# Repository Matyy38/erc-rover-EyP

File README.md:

---
titulo: Rover ERC — subsistema de Electrónica y Potencia
estado: vigente
fecha: 2026-10-26
fuente: migracion.md (árbol y mapeo de los cuatro documentos fuente)
---

# Rover ERC — Electrónica y Potencia

Documentación del subsistema de Electrónica y Potencia del rover del European Rover Challenge
(IEEE ITBA I+D). Dos frentes: el **rover final** (40 kg, bus de 24 V, swerve de 4 ruedas) y el **modelo a
escala**, que es un instrumento de medición para cerrar la especificación de motores sin comprar
motores de tamaño real a ciegas.

**Empezá por [00-contexto/00-contexto-maestro.md](00-contexto/00-contexto-maestro.md).** Tiene el
estado, los conflictos abiertos y el mapa.

---

## Árbol

```
rover-erc/
├── README.md
├── CLAUDE.md
├── 00-contexto/
│   ├── 00-contexto-maestro.md
│   ├── 01-alcance-y-fronteras.md
│   ├── 02-filosofia-de-diseno.md
│   ├── 03-conflictos-abiertos.md
│   ├── 04-decisiones-descartadas.md
│   └── 05-principios-transversales.md
├── 10-rover-final/
│   ├── 10-locomocion/
│   │   ├── requisitos-motor.md
│   │   └── candidatos-motores.md
│   └── 20-potencia/
│       ├── presupuesto-corriente.md
│       └── cableado-y-protecciones.md
├── 20-modelo-escala/
│   ├── 00-estado-actual.md
│   ├── 10-metodologia-similitud.md
│   ├── 20-electronica/
│   │   ├── arquitectura-electrica.md
│   │   ├── encoders-pcnt.md
│   │   ├── drivers-bts7960.md
│   │   ├── direccion-swerve-servos.md
│   │   ├── sensado-corriente.md
│   │   ├── protecciones-desacople.md
│   │   ├── tmcs1126-datasheet.pdf
│   │   └── PCNT_ESP32_Guia_Rover.pdf
│   ├── 30-pcb/
│   │   ├── especificacion.md
│   │   ├── decisiones-layout.md
│   │   ├── mapa-conectores.md
│   │   ├── bom.md
│   │   └── pendientes-de-verificacion.md
│   ├── 40-firmware/
│   │   ├── mapa-gpio.md
│   │   ├── test-ads1115/
│   │   └── test-mpu6050/
│   └── 50-ensayos/
│       ├── instrumentacion.md
│       └── plan-de-ensayos.md
├── 30-componentes/
├── 40-proveedores-costos/
├── 90-archivo/
│   ├── analisis-sensado-superado.md
│   ├── migracion-2026-09-16.md
│   └── fuentes-originales/
├── audiovisual-presentacion/
└── pcb_V1/
```

---

## Índice

### 00-contexto

| Archivo | Qué tiene |
|---|---|
| [00-contexto-maestro.md](00-contexto/00-contexto-maestro.md) | Documento raíz: estado de los dos frentes, conflictos abiertos, instrumentación, próximos pasos y mapa del repo. |
| [01-alcance-y-fronteras.md](00-contexto/01-alcance-y-fronteras.md) | Qué entra y qué no en el subsistema, con la tabla de interfaces con Mecánica. |
| [02-filosofia-de-diseno.md](00-contexto/02-filosofia-de-diseno.md) | Las reglas no negociables y dónde se aplica cada una. |
| [03-conflictos-abiertos.md](00-contexto/03-conflictos-abiertos.md) | Los tres conflictos que bloquean decisiones y la consulta consolidada a Mecánica. |
| [04-decisiones-descartadas.md](00-contexto/04-decisiones-descartadas.md) | Tabla única de lo que se evaluó y no quedó, con el motivo. |
| [05-principios-transversales.md](00-contexto/05-principios-transversales.md) | Las catorce reglas ganadas en el proyecto que aplican más allá de su caso. |

### 10-rover-final

| Archivo | Qué tiene |
|---|---|
| [10-locomocion/requisitos-motor.md](10-rover-final/10-locomocion/requisitos-motor.md) | Torque, velocidad y potencia por rueda; discrepancias de diámetro; implicancias eléctricas. |
| [10-locomocion/candidatos-motores.md](10-rover-final/10-locomocion/candidatos-motores.md) | Estado por candidato, criterio de reducción y criterio de búsqueda del reemplazo. |
| [20-potencia/presupuesto-corriente.md](10-rover-final/20-potencia/presupuesto-corriente.md) | Del torque medido a la corriente de la PDB: escenarios, techo de tracción, potencia continua. |
| [20-potencia/cableado-y-protecciones.md](10-rover-final/20-potencia/cableado-y-protecciones.md) | Calibres, fusibles y la cadena conector-fusible-cable del rover final. |

### 20-modelo-escala

| Archivo | Qué tiene |
|---|---|
| [00-estado-actual.md](20-modelo-escala/00-estado-actual.md) | Estado de validación de la placa por bloque y cambios confirmados respecto del PDF. |
| [10-metodologia-similitud.md](20-modelo-escala/10-metodologia-similitud.md) | λ vigente, revisión de escala por la masa real, altura del CM y constantes recalculadas. |
| [20-electronica/arquitectura-electrica.md](20-modelo-escala/20-electronica/arquitectura-electrica.md) | Cadena de potencia, rieles y presupuesto del riel de 3,3 V. |
| [20-electronica/encoders-pcnt.md](20-modelo-escala/20-electronica/encoders-pcnt.md) | Acondicionamiento de los ocho canales y uso del periférico PCNT. |
| [20-electronica/drivers-bts7960.md](20-modelo-escala/20-electronica/drivers-bts7960.md) | Habilitaciones, estado del canal 4 en el arranque (V1) y desacople local. |
| [20-electronica/direccion-swerve-servos.md](20-modelo-escala/20-electronica/direccion-swerve-servos.md) | Margen del riel de servos (V3), el PTC único y el estado en el arranque. |
| [20-electronica/sensado-corriente.md](20-modelo-escala/20-electronica/sensado-corriente.md) | TMCS1126B4: qué mide, rango, acondicionamiento, umbral de OC (V9) y calibración. |
| [20-electronica/protecciones-desacople.md](20-modelo-escala/20-electronica/protecciones-desacople.md) | Capas de protección, polaridad inversa (V2), TVS (V5, V6), inrush del relé (V7). |
| [20-electronica/tmcs1126-datasheet.pdf](20-modelo-escala/20-electronica/tmcs1126-datasheet.pdf) | Hoja de datos del TMCS1126 (SBOSAF3D). |
| [20-electronica/PCNT_ESP32_Guia_Rover.pdf](20-modelo-escala/20-electronica/PCNT_ESP32_Guia_Rover.pdf) | Guía de uso del periférico PCNT del ESP32 para los encoders. |
| [30-pcb/especificacion.md](20-modelo-escala/30-pcb/especificacion.md) | Datos generales, corrientes de diseño y anchos de pista. |
| [30-pcb/decisiones-layout.md](20-modelo-escala/30-pcb/decisiones-layout.md) | Masas en estrella, ruteo del TMCS1126, potencia, analógico y mecánica. |
| [30-pcb/mapa-conectores.md](20-modelo-escala/30-pcb/mapa-conectores.md) | Tabla completa de J1 a J19, calibre y fusible del cable soldado en J1 y J4..J7, y convenciones de cableado. |
| [30-pcb/bom.md](20-modelo-escala/30-pcb/bom.md) | Lista por referencia, ítems sin valor definido y compras fuera de placa. |
| [30-pcb/pendientes-de-verificacion.md](20-modelo-escala/30-pcb/pendientes-de-verificacion.md) | Los doce puntos V1 a V12, cómo se confirma cada uno y dónde se discute. |
| [40-firmware/mapa-gpio.md](20-modelo-escala/40-firmware/mapa-gpio.md) | **Fuente única de verdad del pinout**, con la estrategia de arranque seguro. |
| [40-firmware/test-ads1115/](20-modelo-escala/40-firmware/test-ads1115/test-ads1115.ino) | Prueba simple del ADS1115: escaneo I2C y tensión de los cuatro canales cada 0,5 s. |
| [40-firmware/test-mpu6050/](20-modelo-escala/40-firmware/test-mpu6050/test-mpu6050.ino) | Prueba del MPU6050: escaneo I2C, prueba estática con pasa / no pasa, ángulos a 100 Hz. |
| [50-ensayos/instrumentacion.md](20-modelo-escala/50-ensayos/instrumentacion.md) | Cadena de medición, tiro en barra, instrumento externo y riesgos de medición. |
| [50-ensayos/plan-de-ensayos.md](20-modelo-escala/50-ensayos/plan-de-ensayos.md) | Ensayo de ángulo de deslizamiento, Ensayo A fuera de la PDB y próximos pasos. |

### Carpetas por llenar y archivo

| Archivo | Qué tiene |
|---|---|
| [30-componentes/README.md](30-componentes/README.md) | Ficha por componente y enlaces a hojas de datos. Vacía. |
| [40-proveedores-costos/README.md](40-proveedores-costos/README.md) | Proveedores y costos de importación. Vacía. |
| [90-archivo/README.md](90-archivo/README.md) | Versiones superadas y ramas muertas. **No usar como fuente.** |
| [90-archivo/analisis-sensado-superado.md](90-archivo/analisis-sensado-superado.md) | El análisis que suponía que el TMCS1126 medía el total de la PDB, con su nota de trazabilidad. |
| [90-archivo/migracion-2026-09-16.md](90-archivo/migracion-2026-09-16.md) | Plan con el que se armó este árbol a partir de los cuatro documentos fuente. |
| [90-archivo/fuentes-originales/README.md](90-archivo/fuentes-originales/README.md) | Los cuatro documentos previos a la migración, sin tocar. |

### Material para el equipo

| Archivo | Qué tiene |
|---|---|
| [audiovisual-presentacion/guia-ingreso-EyP-2026-09.docx](audiovisual-presentacion/guia-ingreso-EyP-2026-09.docx) | Guía de ingreso: resumen del repo para ponerse al día. Corte al 28-sep-2026; si no coincide con el repo, manda el repo. |
| [audiovisual-presentacion/presentacion-ingreso-EyP-2026-09.pptx](audiovisual-presentacion/presentacion-ingreso-EyP-2026-09.pptx) | Presentación de ingreso al subsistema. |
| [pcb_V1/](pcb_V1/) | Proyecto de KiCad de la placa del modelo, para descargar. El análisis está en `20-modelo-escala/`. |

---

## Reglas de trabajo sobre el repo

- **El mapa de GPIO es fuente única de verdad.** Si una tabla de pines aparece en otro archivo, ese
  archivo enlaza al mapa, no lo copia.
- **Los puntos V1 a V12 son hipótesis, no defectos.** Al cerrar uno, se actualiza su fila con el
  resultado de la medición.
- **La placa ya está fabricada y soldada.** Toda propuesta de cambio dice si es un corte y un puente,
  un componente a reemplazar, o un rediseño.
- **Los archivos de KiCad están en `pcb_V1/` para descargar.** Lo que salió de analizarlos está
  asentado en markdown: los datos se buscan ahí.
- **Cada dato técnico tiene un solo dueño.** El contexto maestro es un índice de estado: resume y
  enlaza, no copia números. Si hay diferencia, manda el archivo de detalle.
- **`90-archivo/` es historia.** No se usa como fuente.

## Convenciones

- Contenido en español. Nombres de archivo en minúscula, sin tildes ni espacios, con guiones.
- Carpetas numeradas para forzar orden de lectura.
- Frontmatter YAML con `titulo`, `estado`, `fecha` y `fuente` en cada archivo.
- Enlaces markdown relativos, nunca wikilinks.
- Entre 40 y 400 líneas por archivo de contenido. Por debajo de 40, fusionar con el contiguo.
- **Los archivos de KiCad se versionan en `pcb_V1/` solo para descarga.** Lo que sale de
  analizarlos se documenta en markdown.
- Registro de decisiones = tabla de descartados, no ADR formales.
- Dentro de tablas, decimales en texto plano con coma. LaTeX solo fuera de tablas.

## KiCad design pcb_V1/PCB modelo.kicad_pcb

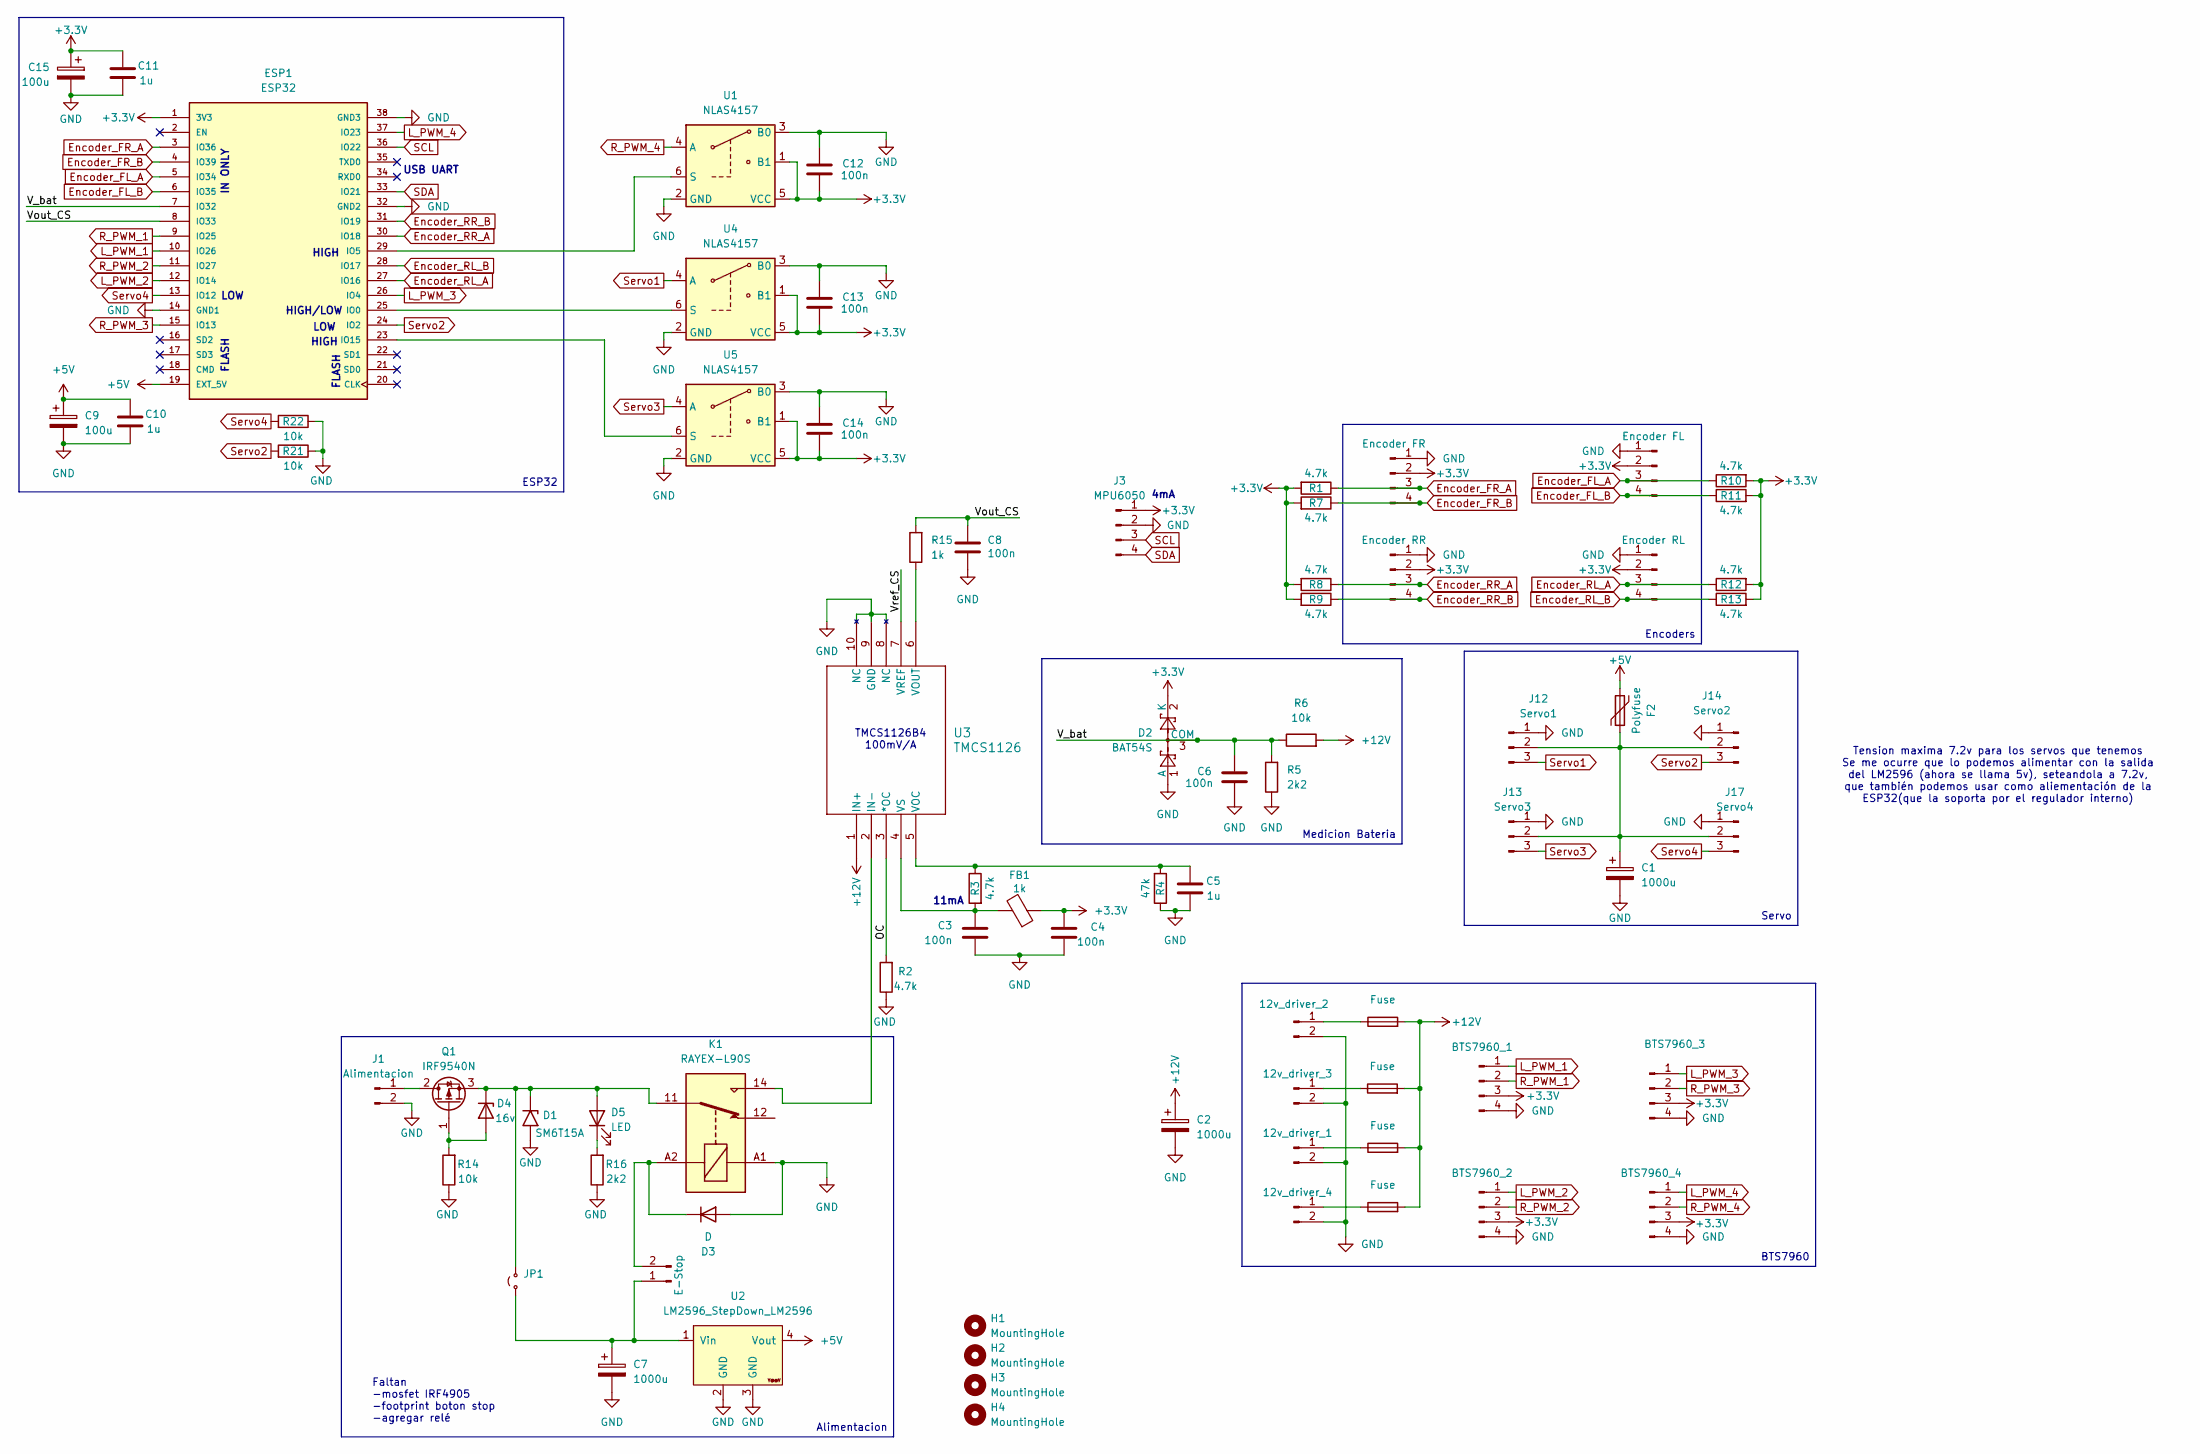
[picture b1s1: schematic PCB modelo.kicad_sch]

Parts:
C1, C2, C7: 1000u; CP_Radial_D10.0mm_P5.00mm
C3, C4: 100n; C_0805_2012Metric
C5, C10, C11: 1u; C_0805_2012Metric
C6, C8: 100n; C_0805_2012Metric_Pad1.18x1.45mm_HandSolder
C9, C15: 100u; C_Radial_D6.3mm_H5.0mm_P2.50mm
C12, C13, C14: 100n; C_0603_1608Metric_Pad1.08x0.95mm_HandSolder
D1: SM6T15A; D_SMB_Handsoldering
D2: BAT54S; SOT-23
D3: D; D_SMA_Handsoldering
D4: 16v; D_MiniMELF
D5: LED; LED_D3.0mm
ESP1: ESP32; esp32_39pin; PARTREV N/A
F2: Polyfuse; RV_Disc_D9mm_W3.3mm_P5mm
F3, F4, F5, F6: Fuse; FuseClip_5x20_ZH266
FB1: 1k; L_0805_2012Metric
H1, H2, H3, H4: MountingHole; MountingHole_3.2mm_M3
J1: Alimentacion; PhoenixContact_MSTBA_2,5_2-G_1x02_P5.00mm_Horizontal
J2: E-Stop; Molex_KK-254_AE-6410-02A_1x02_P2.54mm_Vertical
J3: MPU6050; Molex_KK-254_AE-6410-04A_1x04_P2.54mm_Vertical
J4: 12v_driver_2; Molex_KK-254_AE-6410-02A_1x02_P2.54mm_Vertical
J5: 12v_driver_3; Molex_KK-254_AE-6410-02A_1x02_P2.54mm_Vertical
J6: 12v_driver_1; Molex_KK-254_AE-6410-02A_1x02_P2.54mm_Vertical
J7: 12v_driver_4; Molex_KK-254_AE-6410-02A_1x02_P2.54mm_Vertical
J8: Encoder RR; Molex_KK-254_AE-6410-04A_1x04_P2.54mm_Vertical
J9: Encoder FR; Molex_KK-254_AE-6410-04A_1x04_P2.54mm_Vertical
J10: BTS7960_1; Molex_KK-254_AE-6410-04A_1x04_P2.54mm_Vertical
J11: BTS7960_2; Molex_KK-254_AE-6410-04A_1x04_P2.54mm_Vertical
J12: Servo1; Molex_KK-254_AE-6410-03A_1x03_P2.54mm_Vertical
J13: Servo3; Molex_KK-254_AE-6410-03A_1x03_P2.54mm_Vertical
J14: Servo2; Molex_KK-254_AE-6410-03A_1x03_P2.54mm_Vertical
J15: BTS7960_3; Molex_KK-254_AE-6410-04A_1x04_P2.54mm_Vertical
J16: Encoder FL; Molex_KK-254_AE-6410-04A_1x04_P2.54mm_Vertical
J17: Servo4; Molex_KK-254_AE-6410-03A_1x03_P2.54mm_Vertical
J18: Encoder RL; Molex_KK-254_AE-6410-04A_1x04_P2.54mm_Vertical
J19: BTS7960_4; Molex_KK-254_AE-6410-04A_1x04_P2.54mm_Vertical
JP1: Jumper_2_Small_Open; TestPoint_2Pads_Pitch2.54mm_Drill0.8mm
K1: RAYEX-L90S; Relay_SPDT_RAYEX-L90S
Q1: IRF9540N; TO-220-3_Vertical
R1, R2, R3, R7, R8, R9, R10, R11, R12, R13: 4.7k; R_0805_2012Metric
R4: 47k; R_0805_2012Metric
R5: 2k2; R_0805_2012Metric_Pad1.20x1.40mm_HandSolder
R6: 10k; R_0805_2012Metric_Pad1.20x1.40mm_HandSolder
R14, R21, R22: 10k; R_0805_2012Metric
R15: 1k; R_0805_2012Metric_Pad1.20x1.40mm_HandSolder
R16: 2k2; R_0805_2012Metric
U1, U4, U5: NLAS4157; SOT-363_SC-70-6_tomi
U2: LM2596_StepDown_LM2596; LM2596_buck
U3: TMCS1126; SOIC10_DVG_TEX

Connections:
+3.3V: C4.1, C11.1, C12.1, C13.1, C14.1, C15.1, D2.2 (K), ESP1.1 (3V3), FB1.1, J3.1, J8.2, J9.2, J10.3, J11.3, J15.3, J16.2, J18.2, J19.3, R1.2, R7.2, R8.2, R9.2, R10.2, R11.2, R12.2, R13.2, U1.1 (B1), U1.5 (VCC), U4.1 (B1), U4.5 (VCC), U5.1 (B1), U5.5 (VCC)
+5V: C9.1, C10.1, ESP1.19 (EXT_5V), F2.2, U2.4 (Vout)
+12V: C2.1, F3.2, F4.2, F5.2, F6.2, R6.2, U3.1 (IN+)
/OC: R2.2, U3.3 (*OC)
/V_bat: C6.2, D2.3 (COM), ESP1.7 (IO32), R5.2, R6.1
/Vout_CS: C8.2, ESP1.8 (IO33), R15.2
/Vref_CS: U3.7 (VREF)
Encoder_FL_A: ESP1.5 (IO34), J16.3, R10.1
Encoder_FL_B: ESP1.6 (IO35), J16.4, R11.1
Encoder_FR_A: ESP1.3 (IO36), J9.3, R1.1
Encoder_FR_B: ESP1.4 (IO39), J9.4, R7.1
Encoder_RL_A: ESP1.27 (IO16), J18.3, R12.1
Encoder_RL_B: ESP1.28 (IO17), J18.4, R13.1
Encoder_RR_A: ESP1.30 (IO18), J8.3, R8.1
Encoder_RR_B: ESP1.31 (IO19), J8.4, R9.1
GND: C1.2, C2.2, C3.2, C4.2, C5.2, C6.1, C7.2, C8.1, C9.2, C10.2, C11.2, C12.2, C13.2, C14.2, C15.2, D1.2 (A2), D2.1 (A), D3.2 (A), ESP1.14 (GND1), ESP1.32 (GND2), ESP1.38 (GND3), J1.2, J3.2, J4.2, J5.2, J6.2, J7.2, J8.1, J9.1, J10.4, J11.4, J12.1, J13.1, J14.1, J15.4, J16.1, J17.1, J18.1, J19.4, K1.A1, R2.1, R4.1, R5.1, R14.1, R16.1, R21.1, R22.1, U1.2 (GND), U1.3 (B0), U2.2 (GND), U2.3 (GND), U3.8 (NC), U3.9 (GND), U3.10 (NC), U4.2 (GND), U4.3 (B0), U5.2 (GND), U5.3 (B0)
L_PWM_1: ESP1.10 (IO26), J10.1
L_PWM_2: ESP1.12 (IO14), J11.1
L_PWM_3: ESP1.26 (IO4), J15.1
L_PWM_4: ESP1.37 (IO23), J19.1
unnamed: D1.1 (A1), D4.1 (K), D5.2 (A), JP1.2 (B), K1.11, Q1.3 (S)
unnamed: D3.1 (K), J2.2, K1.A2
unnamed: D4.2 (A), Q1.1 (G), R14.2
unnamed: D5.1 (K), R16.2
unnamed: ESP1.25 (IO0), U4.6 (S)
unnamed: ESP1.29 (IO5), U1.6 (S)
unnamed: ESP1.23 (IO15), U5.6 (S)
unnamed: J1.1, Q1.2 (D)
unnamed: C7.1, J2.1, JP1.1 (A), U2.1 (Vin)
unnamed: F3.1, J4.1
unnamed: F4.1, J5.1
unnamed: F5.1, J6.1
unnamed: F6.1, J7.1
unnamed: C1.1, F2.1, J12.2, J13.2, J14.2, J17.2
unnamed: K1.14, U3.2 (IN-)
unnamed: C5.1, R3.1, R4.2, U3.5 (VOC)
unnamed: R15.1, U3.6 (VOUT)
unnamed: C3.1, FB1.2, R3.2, U3.4 (VS)
R_PWM_1: ESP1.9 (IO25), J10.2
R_PWM_2: ESP1.11 (IO27), J11.2
R_PWM_3: ESP1.15 (IO13), J15.2
R_PWM_4: J19.2, U1.4 (A)
SCL: ESP1.36 (IO22), J3.3
SDA: ESP1.33 (IO21), J3.4
Servo1: J12.3, U4.4 (A)
Servo2: ESP1.24 (IO2), J14.3, R21.2
Servo3: J13.3, U5.4 (A)
Servo4: ESP1.13 (IO12), J17.3, R22.2

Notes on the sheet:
IN ONLY
Faltan -mosfet IRF4905 -footprint boton stop -agregar relé
HIGH
Tension maxima 7.2v para los servos que tenemos Se me ocurre que lo podemos alimentar con la salida del LM2596 (ahora se llama 5v), seteandola a 7.2v, que también podemos usar como aliementación de la ESP32(que la soporta por el regulador interno)
TMCS1126B4 100mV/A
HIGH/LOW
4mA
FLASH
USB UART
11mA
LOW
BTS7960
Alimentacion
Medicion Bateria
Encoders
ESP32
Servo

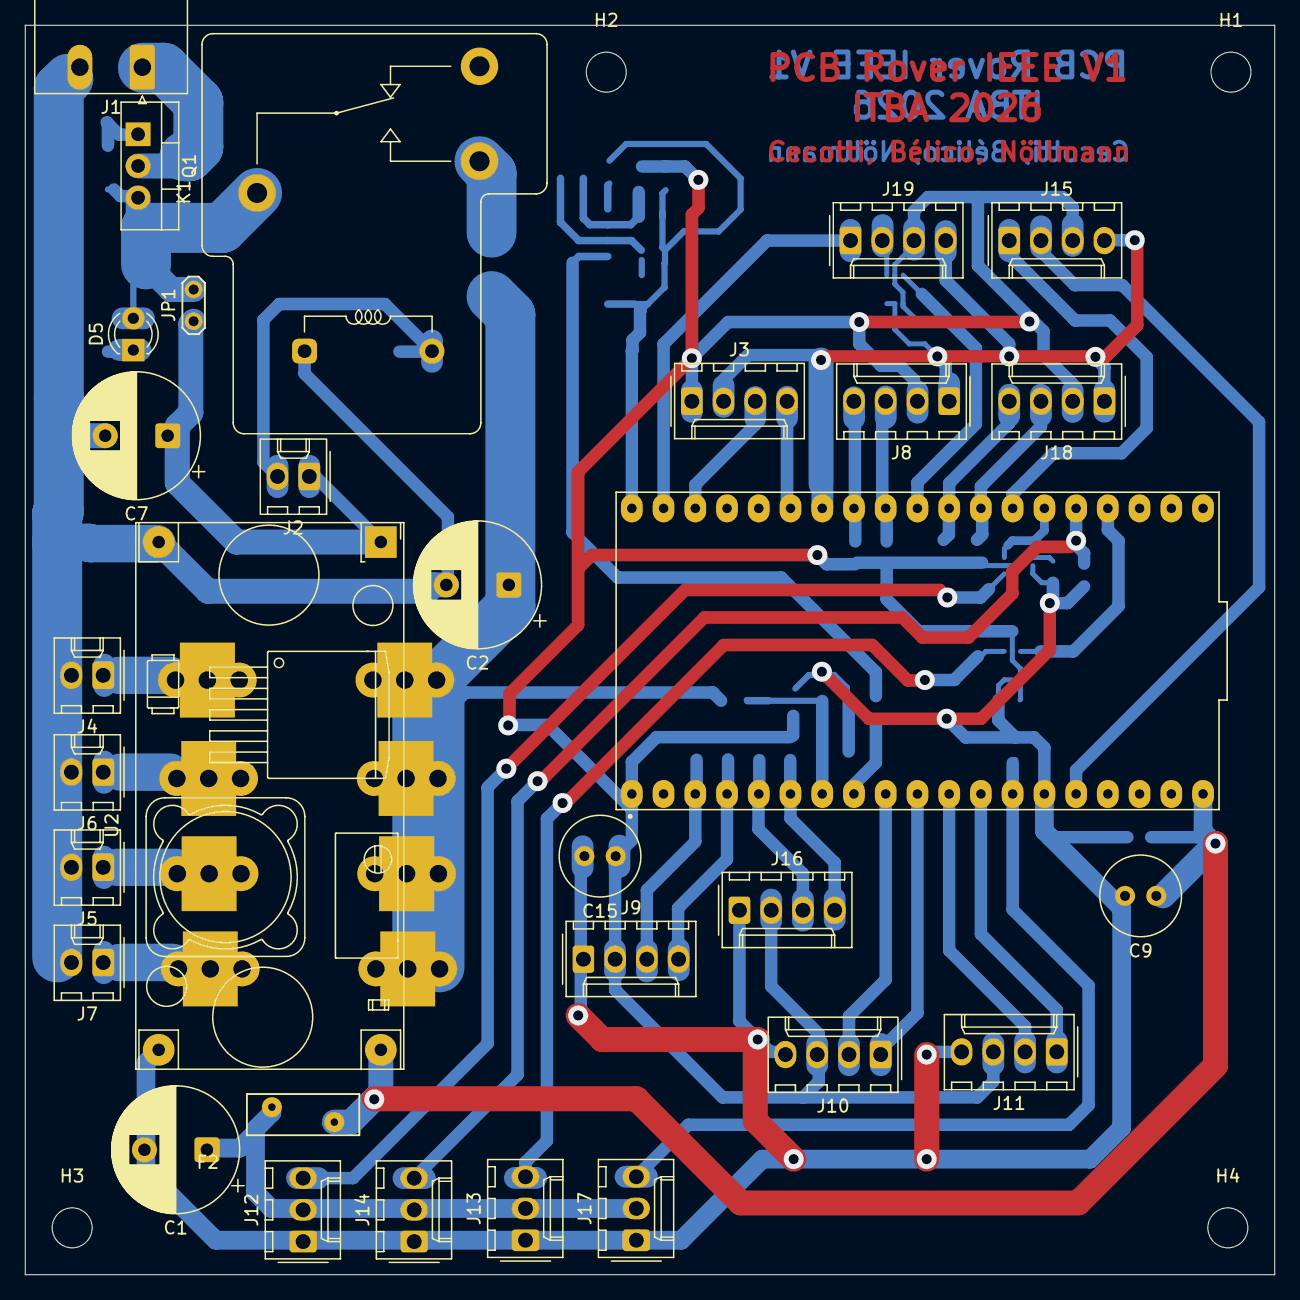
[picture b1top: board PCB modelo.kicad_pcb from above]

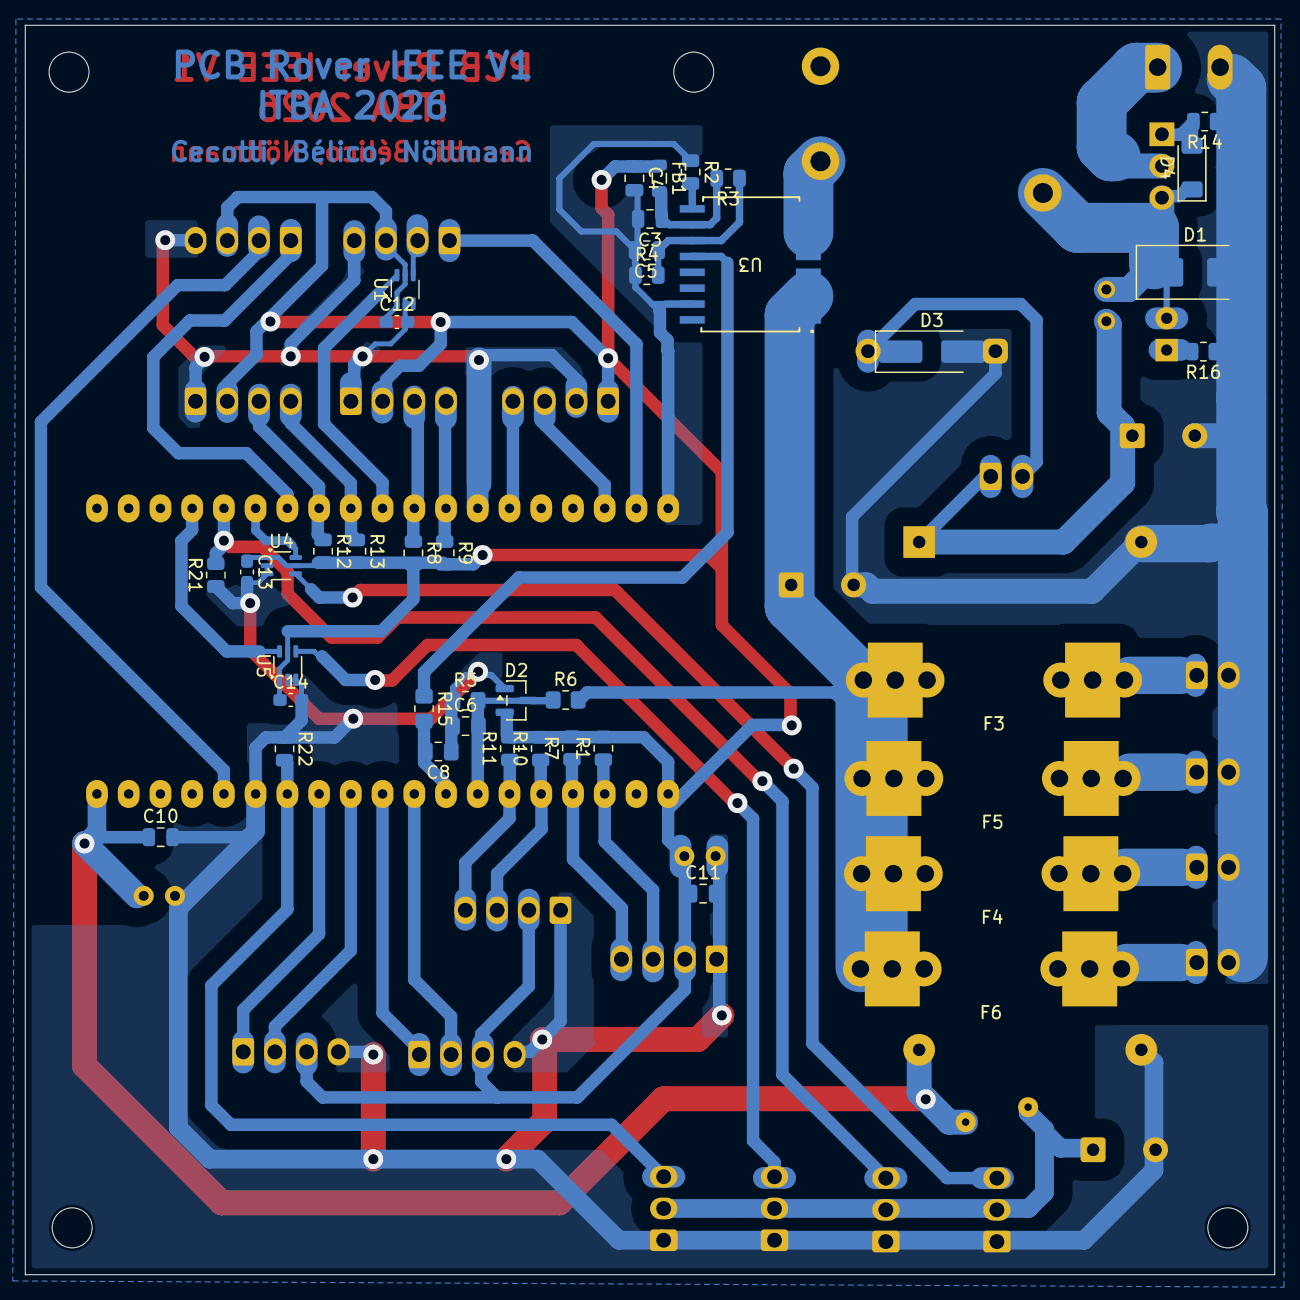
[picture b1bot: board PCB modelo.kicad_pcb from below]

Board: 2 copper layers, 100.0 x 100.0 mm, 76 parts (41 on the bottom side), 47 nets.
